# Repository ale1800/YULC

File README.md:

# YULC (Yes, a USB-C Led Controller)

## Current hw rev: [2.2](https://github.com/ale1800/YULC/blob/main/HW_VERSIONS.md)

## Available [here](https://aaelectronics-shop.com/)!

## You can find [here](https://aaelectronics-docs.com/documentation/yulc/yulc.html) the complete documentation.

**YULC** is your future-proof perfect mate for powering your lightings at 5, 12 or 24V. Thanks to its compact form factor, it can be placed almost everywhere, it features a lot of protections to **ensure safety for both the charger and the strips**, and in the meanwhile, **can provide a lot of juice to feed very power-hungry lights setup.** 
It also boasts an handy **built-in buck regulator** that from a maximum of 24V ensures safe 5V or 12V to your output. This mean that is also possible to use 18,19,...,24V external power supply (USB-C or barrel jack) taking advantage of their higher total power output and converting them to 5V or 12V increasing the output current.
Furthermore, on the back of the board there is a **powerful ESP32-S3, directly programmable from the USB-C**, that allows you to manage even more complex effects and to run heavy tasks.  
So, in few words, **YULC** consists in a full-featured board that can replace a lot of wiring messes, optimizing space and debug time in a reliable way.

## HOW IT WORKS

Here you can have a look to how the power path works:

There are two power stages. The main one for the led stips and one dedicated to the ESP32

Powering all the logic and the ESP32-S3 with a dedicated secondary power stage without relying on the main one ensures that in case of a blowing fuse, everyhitng will still work as expected. So replacing the fuse on-the-fly will be the only thing you'll need to be again ready to go.

## YULC SETTINGS EXPLANATION

1) This is the main jumper that you have to select before anything else and before powering the board. If you join the **"EXT"** pins, YULC will be powered through the barrel jack power supply, not through the USB-C. So you can use a power supply up to 24V and then decide if you want to buck it to 5V or 12V or use it directly to the output bypassing the buck converter. With this selection, you are also able to safely program YULC through the USB-C while powering everything from the external power supply thanks to a back-to-back mosfet configuration. To do that **you have to select 5V from the PD selection voltage (2)**. There will also be those 5V on the board but they won't power anything (To prove that just disconnect the barrel jack power supply and the board will be turned off).
Instead, if you select **"USB"** pins, everything will be powered from the USB-C according to the voltage selected. 
As before, you can choose to buck the voltage to 12 or 5V or use it directly.
> [!CAUTION] 
**When selecting "USB", do not also connect the barrel jack!**.
   
2) USB-C PD Voltage selection. **Note that these voltages are the one you are asking for to the charger, not the ones you'll surely have on the board.** Selecting 20V, if the charger can provide them, the negotiation will end successfully, mosfets will let current flow and everything will be powered on. But if the charger is not able to do that, the negotiation will fail and the board will stay off. To help you debug that, the leds "OK" or "BAD" will lights up according to the negotiation result. Pay attention to the chargers you want to use. It should have a label with the list of voltages it can provide, so be sure to ask for that supported voltages, otherwise the negotiation will fail. Also consider the amount of power you need for your led strips and the power the charger can give.
**Chargers with the USB-A output will not work, even selecting 5V on YULC. Only Type-C Power Delivery chargers are compatible**
> [!IMPORTANT]  
Eg. If you have 5V strips like WS2812b and you want 6A at the output (so 30W), **be sure to ask the for a voltage/current combo the charger can offer that can give those 30W and than buck it to 5V through the converter to have the current you want at the output.**

> [!IMPORTANT]  
Be sure to select the closest combination of power and input voltage to what you need. If you need the buck IC to regulate at 5V, an input voltage of 9V or 12V will be better than a 24V from the heating point of view. The voltage difference (Vin - Vout) is smaller, so the inductor is "less stressed" -> less ripple current -> less heat. So you need the best trade-off with a quite close input voltage and enough power for your application.

3) This is the buck converter output regulation. Populate horizontally the pairs of pins according to the voltage you want to have at the output. If your input is lower or same as the output, just do not use the buck converter and route it directly but keep it populated even if you don't use it. The buck IC will automatically enter in an energy save mode when the load is really small or even is not present.
**The same voltage will be shared across the two channels**
You can source up to 20A from the IC.
> [!IMPORTANT]  
**With high watts at the output the board's temperature will increase, so please always use the given heatsinks (both for the IC and the inductor) and the 5V fan to be on the safe side.**

4) These two fuse holders are not one for channel as it could seem. The two channels share the same fuse. But there are two fuses because you have to select only one at a time according to what output you need. If you need the buck converter you have to populate the **"REGULAT. OUT"** fuse. Otherwise, if you want the input voltage routed directly to the output, populate the **"DIRECT OUT"** one.
These holders are compatible with both the standard automotive blade fuses and the mini blase fuses, but for higher currents the standard blade fuse is suggested thanks to a better contact with the holder's metal
> [!CAUTION]  
**Never populate both of them at the same time, it will short the regulator IC**.

5) YULC's has 10 output terminals, 5 for each channel: **2x Positive terminal, 2x GND terminal, 1x Data terminal**.     
Each terminal can handle up to 15A, so it's heavily suggested to use both the pairs of the positive terminal and negative terminal, to decrease the overall resistance and to inject power easier later in the strips.
Each channel is equipped with a level shifer to its data output and a high side power N-mosfet, in order to save a lot of power for longer strips in the idle state. These mosfets can also be used to control simpler strips through PWM, so you can easily control different combinations of type of strips using both the channels. **Plase attach the given heatinsks to them to keep them cool when switching high currents**

6) YULC exposes also some pins through breadboard-friendly headers. You can use these to connect buttons/microhpones/potentiometers but you can also increase the number of output channels but consider that they don't have level shifters and that you should take the power from the dedicated output terminals
   
 **GPIO Header:**
  
  |   Pin    |  Function |
  |----------|-----------|
  |  GPIO 6 |     IO    |
  |  GPIO 5 |     IO    |
  |  GPIO 4 |     IO    |
  |  GPIO 38 |     IO    |
  |  GPIO 37 |     IO    |
  |  GPIO 36 |     IO    |
  |  3V      |   Power   |
  |  GND     |  Ground   |
  |  GPIO 44   |    TX     |
  |  GPIO 43   |    RX     |
  
 **Used GPIO:**

  | Pin | Function |
  | --- | ---|
  | GPIO 0 (DO) | Boot/User Button |
  |  GPIO 1 (DO) | Led Data 1 |
  |  GPIO 2 (DO) | Led Data 2 |
  |  GPIO 47 (DO) | Mosfet 1 |
  | GPIO 21 (DO) | Mosfet 2 |
  | GPIO 7 (AI) | Fuse sense |

## YULC'S FISRT CONFIGURATION

According to your type of setup, you'll want to set YULC and strips to be powered in the the best way possibile.
Follow this steps to determine all the jumpers selection you need according to how [they work](#yulc-settings-explanation):

> [!WARNING]  
**Be sure to power YULC only after you've set everything up, do not change PD and buck output voltages on the fly, neither the first jumper**

**Only after you are done with jumpers and fuse selections you can mount the [3D printed enclosure](https://github.com/ale1800/YULC/blob/main/ENCLOSURES.md), because once it's mounted, you'll have limited access to them.**

## SOFTWARE CONFIGURATION
- **YULC with [WLED](#wled)**
- ...

### WLED
Wled for YULC is a manually compiled build, based on the **v0.15.0-b5 "Kosen"**. It features 2 usermods: [Audio Reactive](https://kno.wled.ge/advanced/audio-reactive/) and [MultiRelay](https://mm.kno.wled.ge/usermods/MultiRelay/).

<center>
   
</center>

**AUDIO REACTIVE**
 
Thanks to the powerful ESP32-S3, you can really take adavantage of this integration while driving complex effects on really long strip. Yuo have multiple pins on the exposed header that you can use to read an I2S microphone.

**MULTI RELAY**

Natively WLED only support one pin (usually connected to a relay) to physically turn on and off the light strips. While you can always use one of the exposed pins to wire an external relay, the built-in hardware already allows you to drive the two channels independently and each with its own power mosfet to toggle the strips. And thanks to this usermod, you can fully take advantage of it.
This is valid if you want to connect two addressable strips, but, for example, if you want to connect one digital strip and an anlog one, WLED already manage this without any external software. You would only need to set one mosfet as the main relay, and the other one as a PWM driving signal.
YULC offers a great versatility from this point of view.

So, to configure two digital strip go to **Config -> LED Preferences** and set everything up like the following picture with your own strips type and lengths. Also check **"Make a segment for each output"**
<center>

</center>

Now go back **to Config -> Usermods** and, again, follow the picture, then save. This usermod has 4 pre-defined relays, but you only need the first two. **Pin 47 is linked to Channel 1** (DATA 1 on the PCB) and pin **21 to Channel 2**. Check also **"External"** on both, so we can control these relays through the dedicated APIs.
<center>

</center>
At this point we can physically toggle both segments through built-in mosfets combining both WLED and Multi Relay JSON API. Keep in mind that the WLED main button will still turn off all the segments at once.
The calls you need are:

```yaml
//Switching on the mosfet #0 to power the first segment/strip
curl -X POST -H "Content-Type: application/json" -d ''{"MultiRelay":{"relay":0,"on":true}}'' "http://your-ip-address/json"

//Turning on "software" the segment with ID #0
curl -X POST -H "Content-Type: application/json" -d ''{"seg":[{"id":0,"on":true}]}'' "http://your-ip-address/json/state" 

```
When switching on you'll want to physically turn on the strip before turning on via software. Instead, when switching off, it would be better to reverse the sequence.
Basically there should not be data signals to led strips while they are physically disconnected from the power supply.

If you are an Home Assistant user, you can easily integrate these controls as **light** entities using some shell commands:

```yaml
shell_command:
  strip_1_on: 'curl -X POST -H "Content-Type: application/json" -d ''{"seg":[{"id":0,"on":true}]}'' "http://your-ip-address/json/state"'
  strip_1_mos_on: 'curl -X POST -H "Content-Type: application/json" -d ''{"MultiRelay":{"relay":0,"on":true}}'' "http://your-ip-address/json"'
  strip_1_off: 'curl -X POST -H "Content-Type: application/json" -d ''{"seg":[{"id":0,"on":false}]}'' "http://your-ip-address/json/state"'
  strip_1_mos_off: 'curl -X POST -H "Content-Type: application/json" -d ''{"MultiRelay":{"relay":0,"on":false}}'' "http://your-ip-address/json"'
  strip_2_on: 'curl -X POST -H "Content-Type: application/json" -d ''{"seg":[{"id":1,"on":true}]}'' "http://your-ip-address/json/state"'
  strip_2_mos_on: 'curl -X POST -H "Content-Type: application/json" -d ''{"MultiRelay":{"relay":1,"on":true}}'' "http://your-ip-address/json"'
  strip_2_off: 'curl -X POST -H "Content-Type: application/json" -d ''{"seg":[{"id":1,"on":false}]}'' "http://your-ip-address/json/state"'
  strip_2_mos_off: 'curl -X POST -H "Content-Type: application/json" -d ''{"MultiRelay":{"relay":1,"on":false}}'' "http://your-ip-address/json"'
    
light:
  - platform: template
    lights:
      strip_1:
        turn_on:
          - service: shell_command.strip_1_mos_on
          - service: shell_command.strip_1_on
        turn_off:
          - service: shell_command.strip_1_off
          - service: shell_command.strip_1_mos_off
      strip_2:
        turn_on:
          - service: shell_command.strip_2_mos_on
          - service: shell_command.strip_2_on
        turn_off:
          - service: shell_command.strip_2_off
          - service: shell_command.strip_2_mos_off
```

Now you have two completely separated strips from every point of view.

## License

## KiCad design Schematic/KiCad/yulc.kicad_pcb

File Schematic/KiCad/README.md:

This is not the definitive version of the board. There are still some things to fix.
Please do not use this for produciton

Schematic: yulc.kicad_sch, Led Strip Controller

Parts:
C1, C9, C14, C15, C19, C21: 0.1u; C_0603_1608Metric; LCSC C14663
C2, C3, C4, C5, C6, C7, C22, C23, C24, C25, C26, C27, C28, C29: 22u; C_0805_2012Metric; LCSC C45783
C8: 4.7u; C_0603_1608Metric; LCSC C19666
C10, C11, C12, C13: 1u; C_0603_1608Metric; LCSC C15849
C16: 100n; C_0603_1608Metric; LCSC C14663
C17: 56p; C_0603_1608Metric; LCSC C39148
C18, C20, C30, C31, C32, C33, C34: 10u; C_0603_1608Metric; LCSC C96446
D1, D2: LED_Small; LED_0603_1608Metric; LCSC C5123548
D3: ESDA25W; SOT-323_SC-70; LCSC C3021136
D4: LED_Small; LED_0603_1608Metric; LCSC C965799
D5: D_SMB; LCSC C2836928
D8: D_SMA; LCSC C383698
F1: DIR; FUSE-TH_XF-508P-A-B; LCSC C19727304
F3: REG; FUSE-TH_XF-508P-A-B; LCSC C19727304
IC1: SiC431AED-T1-GE3; SiC431AEDT1GE3; Mouser Part Number 78-SIC431AED-T1-GE3
IC2, IC3: 74LV1T34GWH; 74LV1_SOT65P212X110-5N; Mouser Part Number 771-74LV1T34GWH
J1: USB_C_Receptacle; USB_C_Receptacle_G-Switch_GT-USB-7010ASV; LCSC C165948
J3: Conn_01x03_Pin; PinHeader_1x03_P2.00mm_Vertical; LCSC C22438286
J4: Barrel_Jack; DC-IN-TH_DC-S014A-D025-20A; LCSC C7464928
J5: Conn_02x02_Counter_Clockwise; PinSocket_2x02_P2.00mm_Vertical; LCSC C2905988
J6: Conn_02x05_Odd_Even; PinHeader_2x05_P2.00mm_Vertical; LCSC C7501288
J7: Conn_01x02_Pin; JST_PH_B2B-PH-K_1x02_P2.00mm_Vertical; LCSC C131337
J8: Conn_01x05_Pin; PinSocket_1x05_P2.54mm_Vertical
J10, J11: Conn_01x05_Pin; CONN-TH_5P-P3.81_KF124-3.81-5P; LCSC C72336
J13: Conn_01x07_Pin; PinSocket_1x07_P2.54mm_Vertical
L1: 2.2uH; L_Vishay_IHLP-5050; LCSC C2041476
L2: 4.7u; L_1008_2520Metric; LCSC C91237
Q1, Q7: PMOS; PMOS-SOP-8_L4.9-W3.9-P1.27-LS6.0-BL; LCSC C469397
Q4, Q5: NMOS; DFN-8_L5.9-W5.2-P1.27-LS6.2-BL; LCSC C919580
R1, R20: 13k; R_0603_1608Metric; LCSC C22797
R2: 47k; R_0603_1608Metric; LCSC C25819
R3, R12, R17, R24: 4k; R_0603_1608Metric; LCSC C25804
R4: 100K; R_0603_1608Metric; LCSC C25803
R5: 200K; R_0603_1608Metric; LCSC C25811
R6, R10, R13, R35: 10k; R_0603_1608Metric; LCSC C25804
R7, R19: 27k; R_0603_1608Metric; LCSC C22967
R8: 100k; R_0603_1608Metric; LCSC C25803
R9: 1k; R_0603_1608Metric; LCSC C21190
R11, R34: 6.8k; R_0603_1608Metric; LCSC C269697
R21, R22: 4.99k; R_0603_1608Metric; LCSC C23046
R25: 24k; R_0603_1608Metric; LCSC C23352
R26, R33: 56k; R_0603_1608Metric; LCSC C23206
SW1: SW_Push; SW-SMD_TSA245G00D-250; LCSC C2846758
U1: CH224K; ESSOP-10_L4.9-W3.9-P1.0-LS6.0-TL-EP; LCSC C970725
U2: XC6206PxxxMR; SOT-23-3; LCSC C5884132
U3: ESP32-S3-WROOM-1-N16R2; XCVR_ESP32-S3-WROOM-1-N16R2; PARTREV v1.0; LCSC C82899
U4: TPS54202DDC; SOT-23-6; LCSC C191884
U5: USBLC6-2SC6; SOT-23-6; LCSC C2827654
U6: MCP1416; SOT-23-5; LCSC C18195002
U8, U9: MX5014S; SOIC-8_L4.9-W3.9-P1.27-LS6.0-BL; LCSC Part C5359091

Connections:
+3.3V: C11.1, C18.2, C19.2, J8.5, J13.1, R13.2, R17.2, R24.2, U2.2 (VO), U3.2 (3V3)
+5V: C13.2, C17.1, C31.2, C34.2, IC2.5 (VCC), IC3.5 (VCC), J7.1, L2.2, R8.1, U2.3 (VI)
/BOOT: C16.1, U4.6 (BOOT)
/D+: J1.A6 (D+), J1.B6 (D+), U5.3 (I/O2)
/D+_OUT: U3.14 (IO20), U5.4 (I/O2)
/D-: J1.A7 (D-), J1.B7 (D-), U5.1 (I/O1)
/D-_OUT: U3.13 (IO19), U5.6 (I/O1)
/DATA_OUTPUT: IC2.4 (Y), J10.3
/DATA_OUTPUT_2: IC3.4 (Y), J11.3
/EN: IC1.19 (EN)
/FB: C17.2, R7.1, R8.2, R19.1, U4.4 (FB)
/GPIO4: J8.3, U3.4 (IO4)
/GPIO5: J8.2, U3.5 (IO5)
/GPIO6: J8.1, U3.6 (IO6)
/GPIO12: U3.12 (IO8)
/GPIO18: U3.11 (IO18)
/GPIO35: U3.28 (IO35)
/GPIO36: J13.7, U3.29 (IO36)
/GPIO37: J13.6, U3.30 (IO37)
/GPIO38: J13.5, U3.31 (IO38)
/GPIO39: U3.32 (IO39)
/GPIO40: U3.33 (IO40)
/GPIO41: U3.34 (IO41)
/GPIO42: U3.35 (IO42)
/LED_1_VCC: J10.1, J10.2, Q4.3 (S), U8.3 (Source)
/LED_2_VCC: J11.1, J11.2, Q5.3 (S), U9.3 (Source)
/LED_DATA: IC2.2 (A), U3.39 (IO1)
/LED_DATA_2: IC3.2 (A), U3.38 (IO2)
/MOS_1: U3.24 (IO47), U8.2 (Input)
/MOS_2: U3.23 (IO21), U9.2 (Input)
/OUT: D2.1 (K), J3.1, R12.1, U6.5 (OUT)
/PG_C: R6.1, U1.10 (PG), U6.3 (IN)
/RX: J13.3, U3.36 (RXD0)
/SW: IC1.5 (SW_1), IC1.6 (SW_2), IC1.7 (SW_3), IC1.8 (SW_4), IC1.9 (SW_5), L1.1
/SW_5V: C16.2, L2.1, U4.2 (SW)
/TX: J13.2, U3.37 (TXD0)
/VBUS_C: C14.1, D8.1 (A1), J1.A4 (VBUS), J1.A9 (VBUS), J1.B4 (VBUS), J1.B9 (VBUS), Q7.1 (D), R3.1, R9.2, R10.2, U6.2 (Vdd)
/VDD: C10.1, IC1.15 (VDD)
/VDD_C: C12.2, J6.9, R6.2, R9.1, U1.1 (VDD)
/VIN: C1.1, C2.2, C3.2, C15.2, C27.2, C28.2, C29.2, C30.2, D5.1 (A1), F1.1, IC1.1 (VIN_1), IC1.2 (VIN_2), IC1.22 (VIN_3), IC1.26 (VIN_4), J4.1, Q1.1 (D), U4.3 (VIN)
/VOLT_OUT: R34.2, R35.2, U3.7 (IO7)
/V_LED: C32.2, C33.2, F1.2, F3.2, Q4.2 (D), Q5.2 (D), R33.1, U8.1 (V+), U9.1 (V+)
/V_REG: C4.2, C5.2, C6.2, C7.2, C21.1, C22.2, C23.2, C24.2, C25.2, C26.2, F3.1, IC1.18 (VOUT), L1.2, R2.2
Earth: C1.2, C2.1, C3.1, C4.1, C5.1, C6.1, C7.1, C8.1, C10.2, C11.2, C12.1, C13.1, C14.2, C15.1, C18.1, C19.1, C20.1, C21.2, C22.1, C23.1, C24.1, C25.1, C26.1, C27.1, C28.1, C29.1, C30.1, C31.1, C32.1, C33.1, C34.1, D1.1 (K), D3.3 (A), D4.1 (K), D5.2 (A2), D8.2 (A2), IC1.3 (PGND_1), IC1.4 (PGND_2), IC1.13 (PGND_3), IC1.16 (AGND_1), IC1.25 (AGND_2), IC1.27 (PGND_4), IC1.29, IC2.3 (GND), IC3.3 (GND), J1.A1 (GND), J1.A12 (GND), J1.B1 (GND), J1.B12 (GND), J1.S1 (SHIELD), J4.2, J7.2, J8.4, J10.4, J10.5, J11.4, J11.5, J13.4, R1.1, R4.2, R5.2, R7.2, R11.2, R19.2, R20.1, R21.1, R22.1, R25.2, R26.2, R35.1, SW1.1, U1.0 (GND), U2.1 (GND), U3.1 (GND), U3.40 (GND), U3.41_1 (GND), U3.41_2 (GND), U3.41_3 (GND), U3.41_4 (GND), U3.41_5 (GND), U3.41_6 (GND), U3.41_7 (GND), U3.41_8 (GND), U3.41_9 (GND), U4.1 (GND), U5.2 (GND), U6.4 (GND), U8.4 (GND), U9.4 (GND)
unnamed: D1.2 (A), R13.1
unnamed: D2.2 (A), R3.2
unnamed: D3.1 (K1), J1.B5 (CC2), U1.6 (CC2)
unnamed: D3.2 (K2), J1.A5 (CC1), U1.7 (CC1)
unnamed: D4.2 (A), R12.2
unnamed: C9.2, IC1.23 (BOOT)
unnamed: IC1.17 (FB), J5.1, J5.2, R2.1
unnamed: IC1.21 (MODE1), R4.1
unnamed: IC1.20 (MODE2), R5.1
unnamed: C9.1, IC1.24 (PHASE)
unnamed: C8.2, IC1.12 (VDRV)
unnamed: J3.2, Q1.2 (G), Q7.2 (G)
unnamed: J3.3, Q1.3 (S), Q7.3 (S)
unnamed: J5.3, R1.2, R20.2
unnamed: J5.4, R21.2, R22.2
unnamed: J6.3, R26.1
unnamed: J6.5, R25.1
unnamed: J6.7, R11.1
unnamed: J6.4, J6.6, J6.8, J6.10, U1.9 (CFG1)
unnamed: Q4.1 (G), U8.5 (Gate)
unnamed: Q5.1 (G), U9.5 (Gate)
unnamed: R33.2, R34.1
unnamed: R10.1, U1.8 (VBUS)
unnamed: C20.2, R24.1, U3.3 (EN)
unnamed: R17.1, SW1.2, U3.27 (IO0)

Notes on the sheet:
12V
OUTPUT VOLTAGE SELECTOR
5V BUCK REGULATOR
5-9-12-15-20V
POWER STATUS LED
3.3V LDO REGULATOR
USB-C + PD IC
DATA LINE LEVEL SHIFTER
EXT OR USB-C SELECT
MAIN BUCK CONVERTER MAX 24V -> 5V/12V MAX 20A OUTPUT
PD VOLTAGE SELECTOR
ESP32-S3 + LED MOSFET

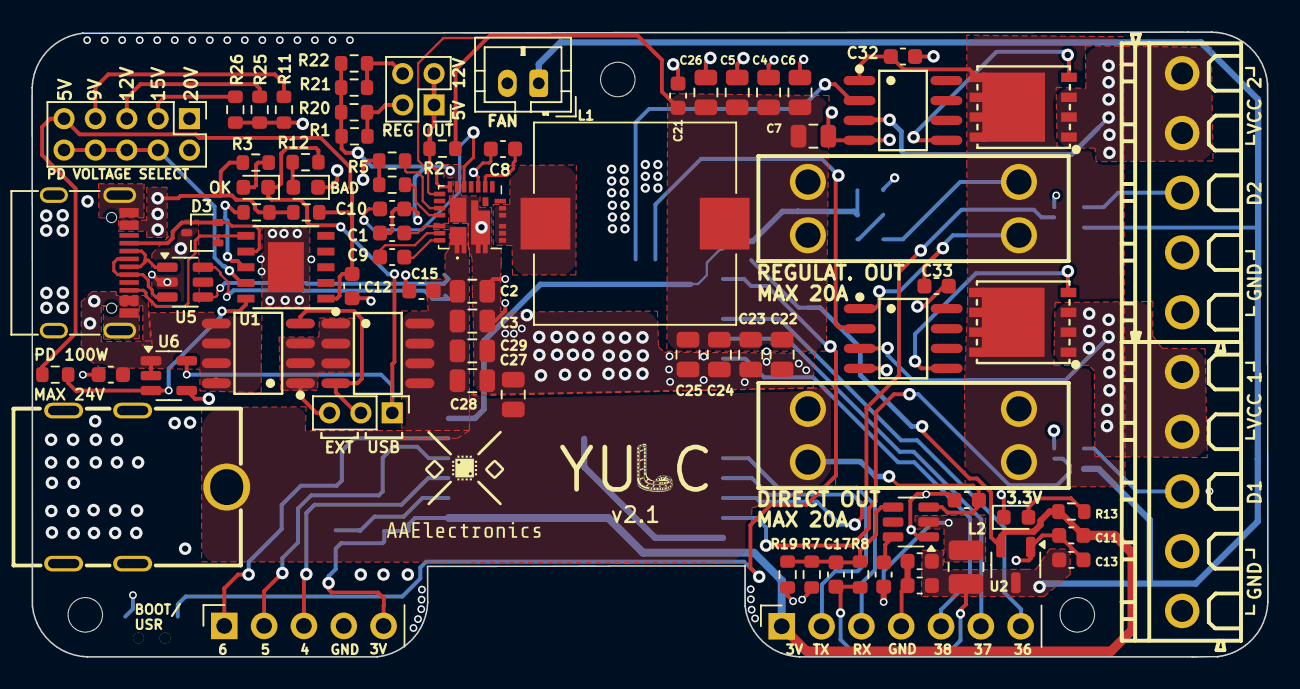
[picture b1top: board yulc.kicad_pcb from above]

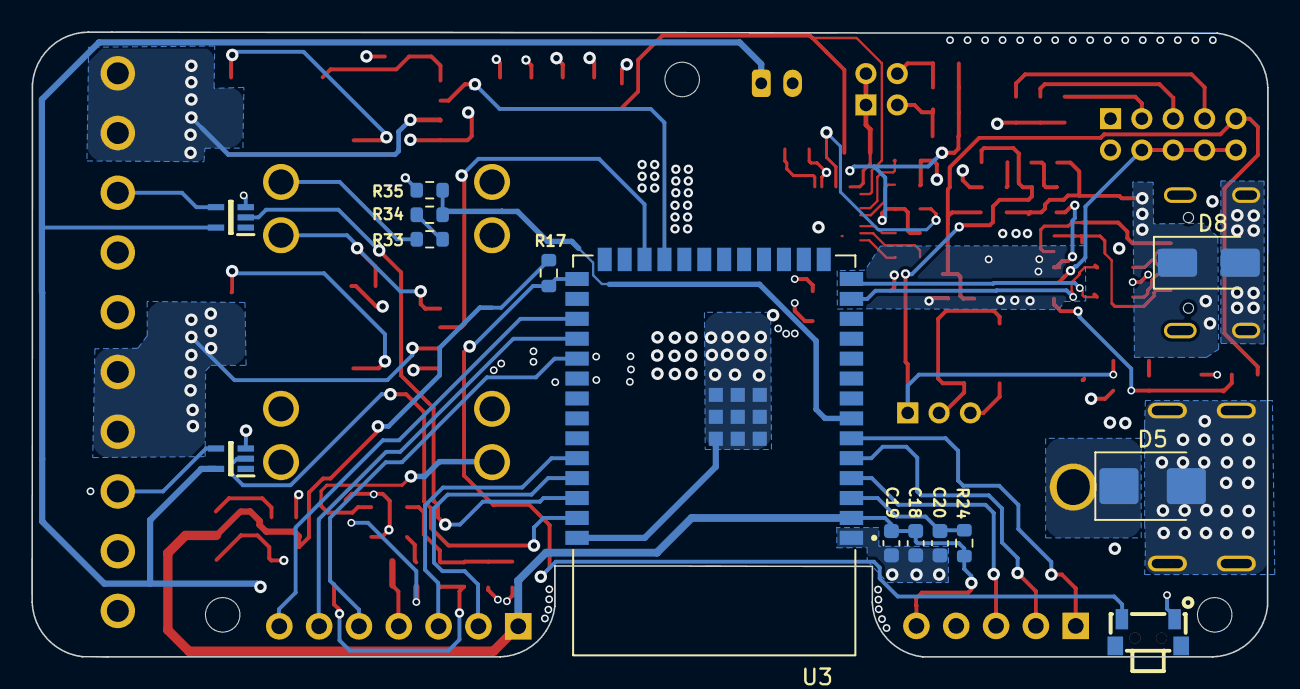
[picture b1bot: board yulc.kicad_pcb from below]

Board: 4 copper layers, 78.8 x 39.8 mm, 94 parts (14 on the bottom side), 61 nets.

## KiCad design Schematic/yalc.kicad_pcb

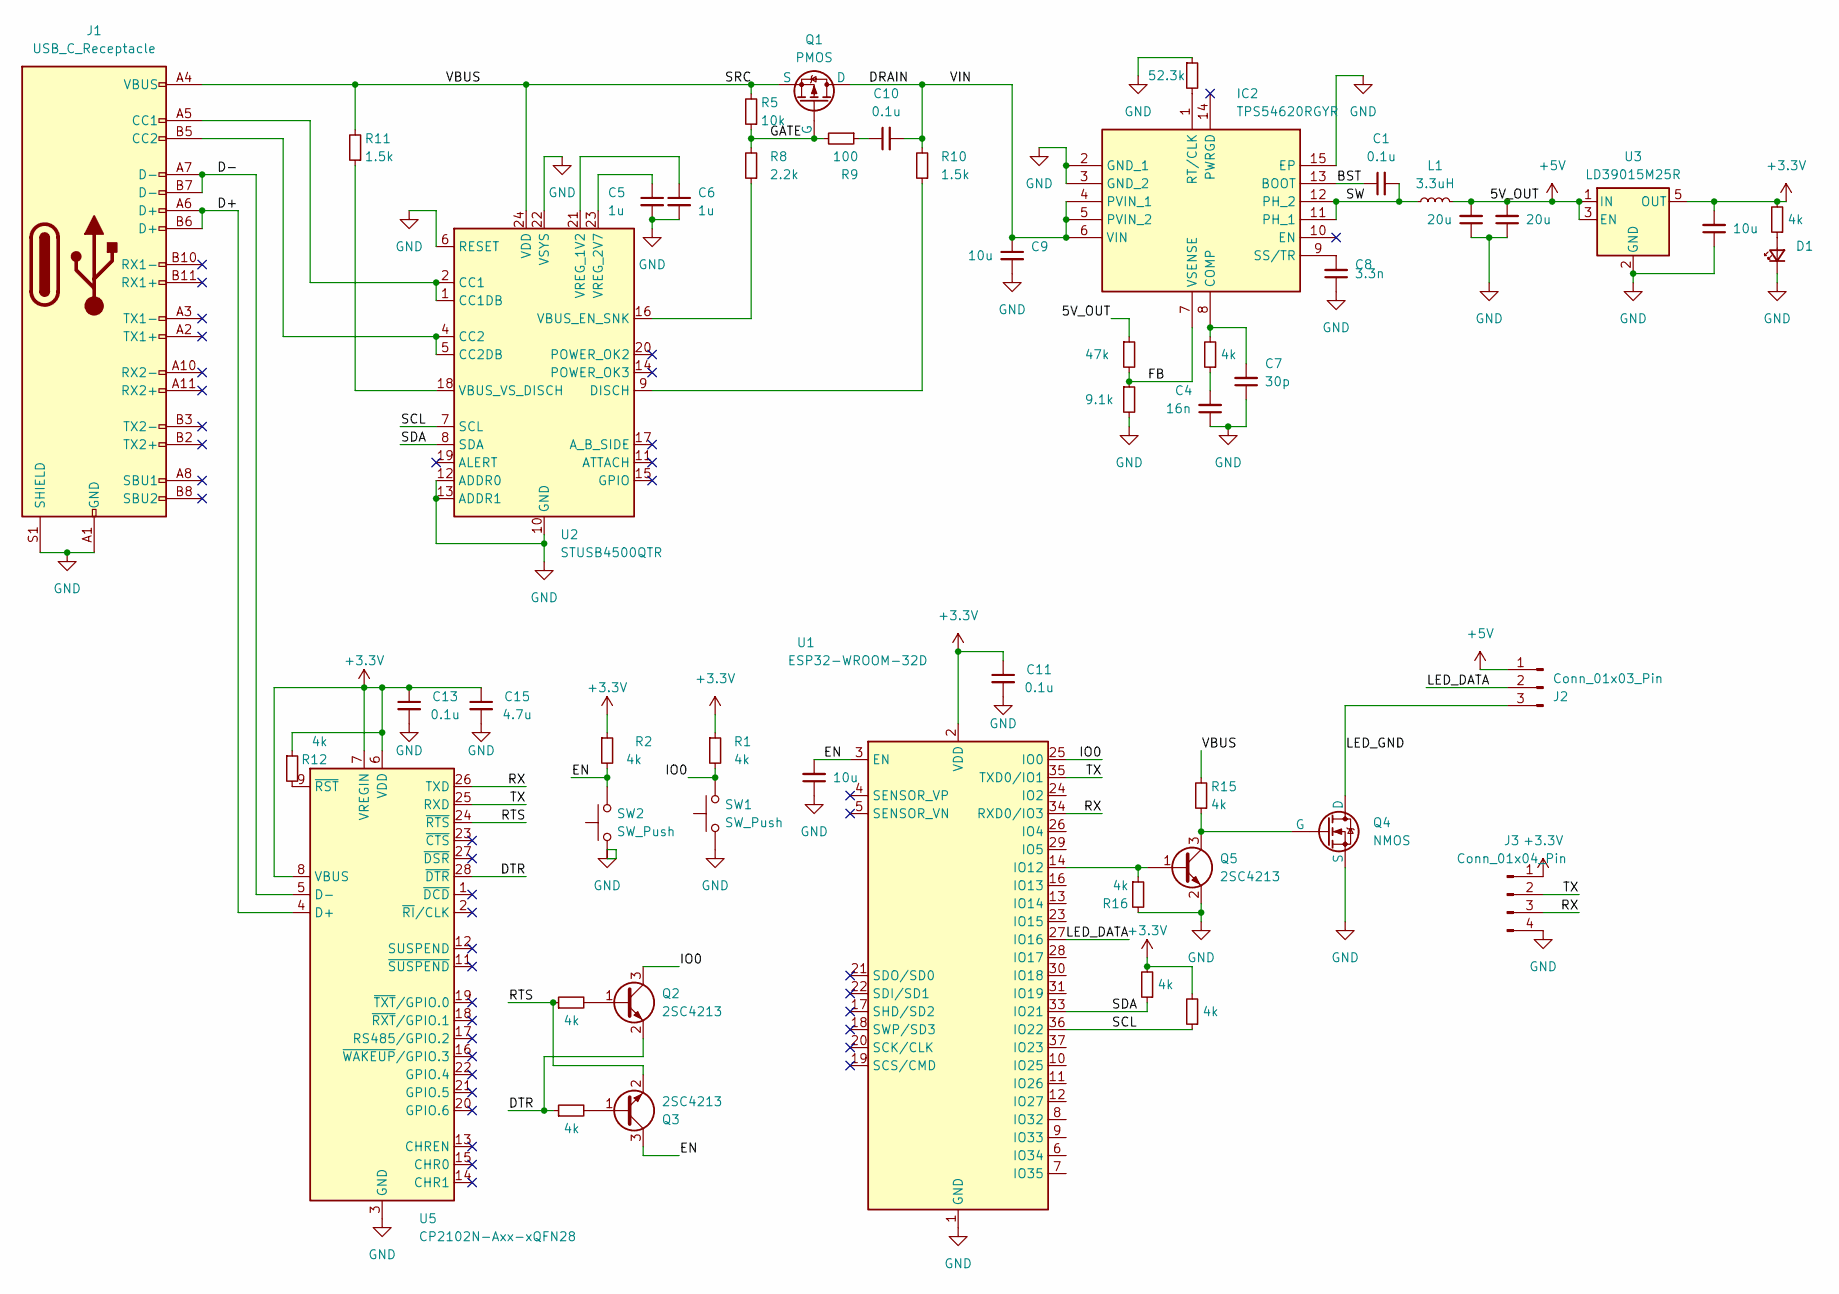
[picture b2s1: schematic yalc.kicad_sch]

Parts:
C1, C10, C11, C13: 0.1u; C_0603_1608Metric; LCSC C14663
C2, C3: 20u; C_0603_1608Metric; LCSC C59461
C4: 16n; C_0603_1608Metric; LCSC C21122
C5, C6: 1u; C_0603_1608Metric; LCSC C15849
C7: 30p; C_0603_1608Metric; LCSC C1658
C8: 3.3n; C_0603_1608Metric_Pad1.08x0.95mm_HandSolder; LCSC C1613
C9, C12, C14: 10u; C_0603_1608Metric; LCSC C96446
C15: 4.7u; C_0603_1608Metric; LCSC C19666
D1: LED_Small; LED_0603_1608Metric
IC2: TPS54620RGYR; SN74CBT3126RGYR; Mouser Part Number 595-TPS54620RGYR
J1: USB_C_Receptacle; USB_C_Receptacle_G-Switch_GT-USB-7010ASV; LCSC C165948
J2: Conn_01x03_Pin; TerminalBlock_bornier-3_P5.08mm
J3: Conn_01x04_Pin; PinSocket_1x04_P1.27mm_Vertical
L1: 3.3uH; L_Coilcraft_XAL8050-223; LCSC C3036137
Q1: PMOS; AON2409; LCSC C6125486
Q2, Q3, Q5: 2SC4213; SOT-323_SC-70; LCSC C516169
Q4: NMOS; TO-252-2_TabPin1; LCSC C148429
R1, R2, R6, R12, R13, R14, R15, R16, R17, R18, R19: 4k; R_0603_1608Metric; LCSC C23018
R3: 47k; R_0603_1608Metric; LCSC C25819
R4: 9.1k; R_0603_1608Metric; LCSC C23260
R5: 10k; R_0603_1608Metric; LCSC C25804
R7: 52.3k; R_0603_1608Metric
R8: 2.2k; R_0603_1608Metric; LCSC C4190
R9: 100; R_0603_1608Metric; LCSC C22775
R10, R11: 1.5k; R_0603_1608Metric; LCSC C22843
SW1, SW2: SW_Push; SW_SPST_CK_RS282G05A3
U1: ESP32-WROOM-32D; LCSC C701341
U2: STUSB4500QTR; QFN-24-1EP_4x4mm_P0.5mm_EP2.7x2.7mm; LCSC C2678061
U3: LD39015M25R; SOT-23-5; LCSC C5446
U5: CP2102N-Axx-xQFN28; QFN-28-1EP_5x5mm_P0.5mm_EP3.35x3.35mm; LCSC C964632

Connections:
+3.3V: C11.1, C12.2, C13.1, C15.1, J3.1, R1.1, R2.1, R12.1, R17.2, R18.2, R19.2, U1.2 (VDD), U3.5 (OUT), U5.6 (VDD), U5.7 (VREGIN), U5.8 (VBUS)
+5V: C2.2, C3.2, J2.1, L1.2, R3.1, U3.1 (IN), U3.3 (EN)
/BST: C1.1, IC2.13 (BOOT)
/D+: J1.A6 (D+), J1.B6 (D+), U5.4 (D+)
/D-: J1.A7 (D-), J1.B7 (D-), U5.5 (D-)
/DRAIN: C9.1, C10.2, IC2.4 (PVIN_1), IC2.5 (PVIN_2), IC2.6 (VIN), Q1.1 (D), R10.2
/DTR: Q2.2 (E), R14.1, U5.28 (~DTR)
/EN: C14.2, Q3.3 (C), R2.2, SW2.2, U1.3 (EN)
/FB: IC2.7 (VSENSE), R3.2, R4.1
/GATE: Q1.2 (G), R5.1, R8.2, R9.2
/IO0: Q2.3 (C), R1.2, SW1.2, U1.25 (IO0)
/LED_DATA: J2.2, U1.27 (IO16)
/LED_GND: J2.3, Q4.2 (D)
/RTS: Q3.2 (E), R13.1, U5.24 (~RTS)
/RX: J3.3, U1.34 (RXD0/IO3), U5.26 (TXD)
/SCL: R19.1, U1.36 (IO22), U2.7 (SCL)
/SDA: R18.1, U1.33 (IO21), U2.8 (SDA)
/SRC: J1.A4 (VBUS), J1.A9 (VBUS), J1.B4 (VBUS), J1.B9 (VBUS), Q1.3 (S), R5.2, R11.2, R15.2, U2.24 (VDD)
/SW: C1.2, IC2.11 (PH_1), IC2.12 (PH_2), L1.1
/TX: J3.2, U1.35 (TXD0/IO1), U5.25 (RXD)
GND: C2.1, C3.1, C4.1, C5.2, C6.2, C7.1, C8.1, C9.2, C11.2, C12.1, C13.2, C14.1, C15.2, D1.1 (K), IC2.2 (GND_1), IC2.3 (GND_2), IC2.15 (EP), J1.A1 (GND), J1.A12 (GND), J1.B1 (GND), J1.B12 (GND), J1.S1 (SHIELD), J3.4, Q4.3 (S), Q5.2 (E), R4.2, R7.1, R16.2, SW1.1, SW2.1, U1.1 (GND), U1.15 (GND), U1.38 (GND), U1.39 (GND), U2.6 (RESET), U2.10 (GND), U2.12 (ADDR0), U2.13 (ADDR1), U2.22 (VSYS), U2.25 (GND), U3.2 (GND), U5.3 (GND), U5.29 (GND)
unnamed: C4.2, R6.1
unnamed: C10.1, R9.1
unnamed: D1.2 (A), R17.1
unnamed: C7.2, IC2.8 (COMP), R6.2
unnamed: IC2.1 (RT/CLK), R7.2
unnamed: C8.2, IC2.9 (SS/TR)
unnamed: J1.A5 (CC1), U2.1 (CC1DB), U2.2 (CC1)
unnamed: J1.B5 (CC2), U2.4 (CC2), U2.5 (CC2DB)
unnamed: Q2.1 (B), R13.2
unnamed: Q3.1 (B), R14.2
unnamed: Q4.1 (G), Q5.3 (C), R15.1
unnamed: Q5.1 (B), R16.1, U1.14 (IO12)
unnamed: R10.1, U2.9 (DISCH)
unnamed: R8.1, U2.16 (VBUS_EN_SNK)
unnamed: R11.1, U2.18 (VBUS_VS_DISCH)
unnamed: C6.1, U2.21 (VREG_1V2)
unnamed: C5.1, U2.23 (VREG_2V7)
unnamed: R12.2, U5.9 (~RST)

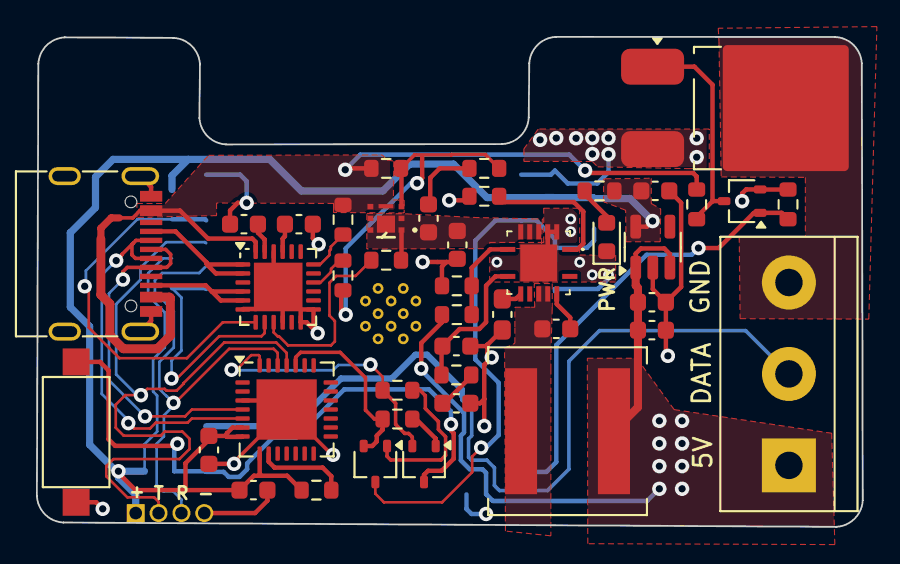
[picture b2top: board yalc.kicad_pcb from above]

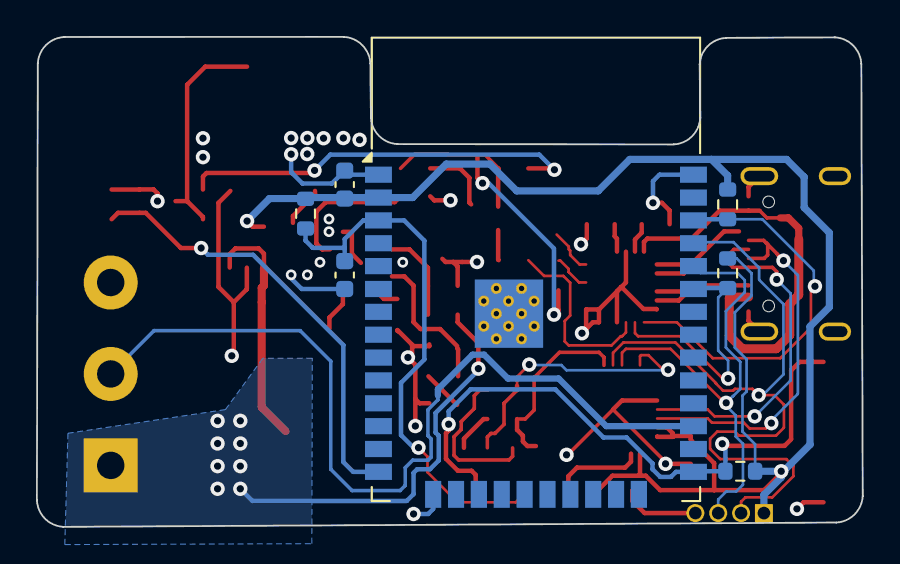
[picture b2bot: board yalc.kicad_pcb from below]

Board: 4 copper layers, 45.9 x 27.2 mm, 50 parts (7 on the bottom side), 39 nets.

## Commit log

2024-04-14 Create prova
2024-06-16 Add files via upload
    Added schematic
2024-07-10 Rename License.md to LICENSE.md
2024-08-04 Add files via upload
    Added dimensions and 3d model
2024-08-08 Added kicad project
2024-09-17 Create t
